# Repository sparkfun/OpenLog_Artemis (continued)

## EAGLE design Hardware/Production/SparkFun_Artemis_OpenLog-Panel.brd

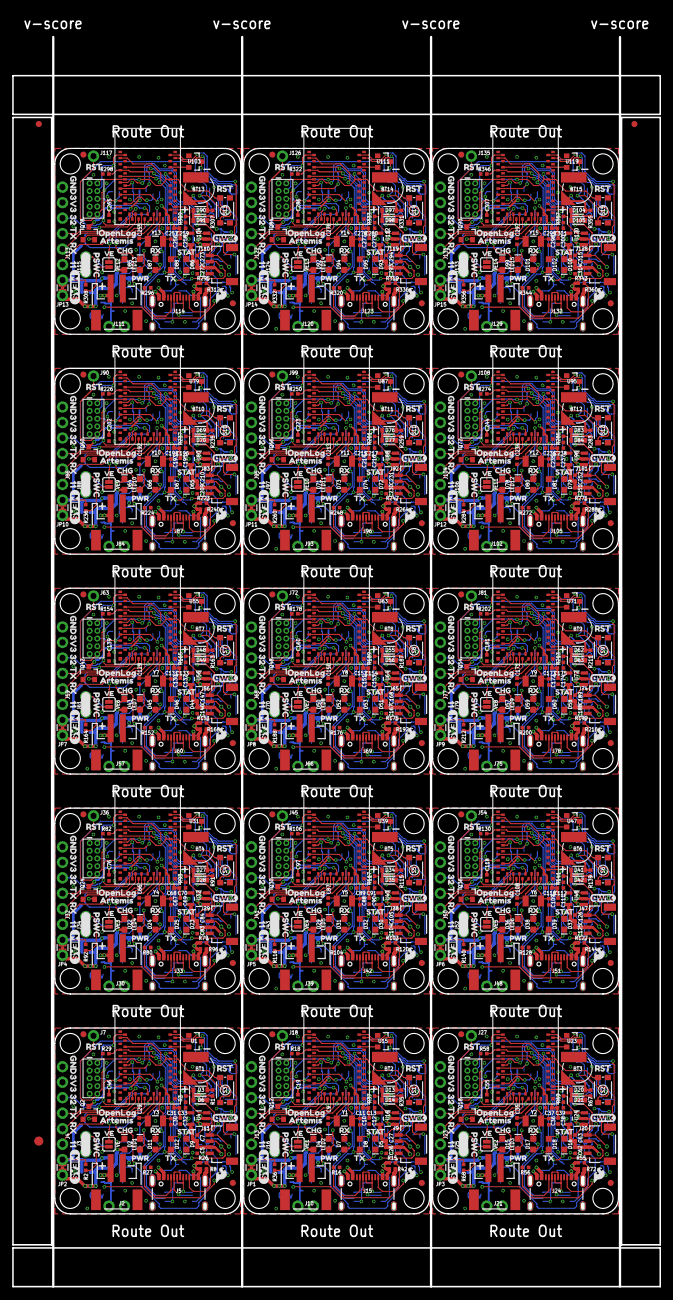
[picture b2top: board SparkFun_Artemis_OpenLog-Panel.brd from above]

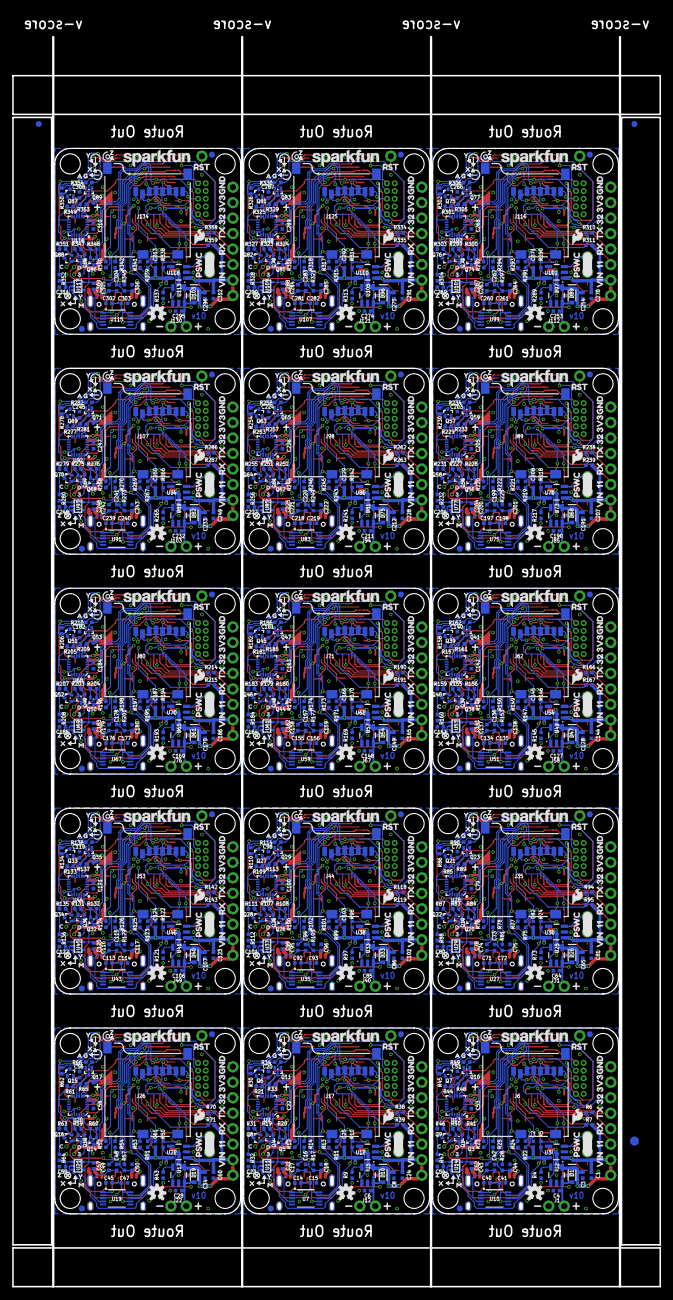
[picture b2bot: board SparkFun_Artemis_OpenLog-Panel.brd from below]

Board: 4 copper layers, 106.2 x 205.0 mm, 2076 parts (1113 on the bottom side), 915 nets.

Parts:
BT1, BT2, BT3, BT4, BT5, BT6, BT7, BT8, BT9, BT10, BT11, BT12, BT13, BT14, BT15: ML414H; ML414H_IV01E
C1, C13, C22, C23, C24, C33, C39, C53, C54, C58, C59, C60, C70, C79, C80, C81, C91, C100, C101, C102, C112, C121, C122, C123, C133, C142, C143, C144, C154, C163, C164, C165, C175, C184, C185, C186, C196, C205, C206, C207, C217, C226, C227, C228, C238, C247, C248, C249, C259, C268, C269, C270, C280, C289, C290, C291, C301, C310, C311, C312: 1.0uF; 0402-TIGHT
C2, C7, C25, C27, C61, C63, C82, C84, C103, C105, C124, C126, C145, C147, C166, C168, C187, C189, C208, C210, C229, C231, C250, C252, C271, C273, C292, C294, C313, C315: 2.2uF; 0402-TIGHT
C3, C4, C6, C8, C28, C34, C64, C65, C85, C86, C106, C107, C127, C128, C148, C149, C169, C170, C190, C191, C211, C212, C232, C233, C253, C254, C274, C275, C295, C296: 4.7uF; 0402-TIGHT
C5, C11, C15, C16, C17, C19, C20, C21, C26, C31, C37, C41, C42, C43, C46, C47, C48, C49, C51, C52, C55, C56, C57, C62, C68, C72, C73, C74, C76, C77, C78, C83, C89, C93, C94, C95, C97, C98, C99, C104, C110, C114, C115, C116, C118, C119, C120, C125, C131, C135, C136, C137, C139, C140, C141, C146, C152, C156, C157, C158, C160, C161, C162, C167, C173, C177, C178, C179, C181, C182, C183, C188, C194, C198, C199, C200, C202, C203, C204, C209, C215, C219, C220, C221, C223, C224, C225, C230, C236, C240, C241, C242, C244, C245, C246, C251, C257, C261, C262, C263, C265, C266, C267, C272, C278, C282, C283, C284, C286, C287, C288, C293, C299, C303, C304, C305, C307, C308, C309, C314: 0.1uF; 0402-TIGHT
C9, C10, C29, C30, C35, C36, C66, C67, C87, C88, C108, C109, C129, C130, C150, C151, C171, C172, C192, C193, C213, C214, C234, C235, C255, C256, C276, C277, C297, C298: 15pF; 0402-TIGHT
C12, C32, C38, C69, C90, C111, C132, C153, C174, C195, C216, C237, C258, C279, C300: 10uF; 0402-TIGHT
C14, C40, C45, C71, C92, C113, C134, C155, C176, C197, C218, C239, C260, C281, C302: 10nF; 0402-TIGHT
C18, C44, C50, C75, C96, C117, C138, C159, C180, C201, C222, C243, C264, C285, C306: 1.0nF; 0402-TIGHT
D1, D3, D10, D13, D19, D20, D26, D27, D33, D34, D40, D41, D47, D48, D54, D55, D61, D62, D68, D69, D75, D76, D82, D83, D89, D90, D96, D97, D103, D104: 3A/10V/280mV; SOD-323
D2, D4, D7, D11, D15, D17, D22, D24, D29, D31, D36, D38, D43, D45, D50, D52, D57, D59, D64, D66, D71, D73, D78, D80, D85, D87, D92, D94, D99, D101: Yellow; LED-0603
D5, D9, D16, D23, D30, D37, D44, D51, D58, D65, D72, D79, D86, D93, D100: BLUE; LED-0603
D6, D14, D21, D28, D35, D42, D49, D56, D63, D70, D77, D84, D91, D98, D105: 1A/23V/620mV; SOD-323
D8, D12, D18, D25, D32, D39, D46, D53, D60, D67, D74, D81, D88, D95, D102: GREEN; LED-0603
E$1, E$2, E$3, E$4: FIDUCIAL-1X2
E$5, E$6: FIDUCIAL-1.5X3
FD1, FD2, FD3, FD4, FD5, FD6, FD7, FD8, FD9, FD10, FD11, FD12, FD13, FD14, FD15, FD16, FD17, FD18, FD19, FD20, FD21, FD22, FD23, FD24, FD25, FD26, FD27, FD28, FD29, FD30, FD31, FD32, FD33, FD34, FD35, FD36, FD37, FD38, FD39, FD40, FD41, FD42, FD43, FD44, FD45, FD46, FD47, FD48, FD49, FD50, FD51, FD52, FD53, FD54, FD55, FD56, FD57, FD58, FD59, FD60: FIDUCIAL1X2; FIDUCIAL-1X2
GND, GND1, GND2, GND3, GND4, GND5, GND6, GND7, GND8, GND9, GND10, GND11, GND12, GND13, GND14: TEST-POINTTP_15TH_THRU; TP_15TH
H1, H2, H3, H4, H5, H6, H7, H8, H9, H10, H11, H12, H13, H14, H15, H16, H17, H18, H19, H20, H21, H22, H23, H24, H25, H26, H27, H28, H29, H30, H31, H32, H33, H34, H35, H36, H37, H38, H39, H40, H41, H42, H43, H44, H45, H46, H47, H48, H49, H50, H51, H52, H53, H54, H55, H56, H57, H58, H59, H60: STAND-OFF
J1, J3, J12, J16, J22, J25, J31, J34, J40, J43, J49, J52, J58, J61, J67, J70, J76, J79, J85, J88, J94, J97, J103, J106, J112, J115, J121, J124, J130, J133: 1X02_NO_SILK
J2, J10, J21, J30, J39, J48, J57, J66, J75, J84, J93, J102, J111, J120, J129: JST-2-SMD
J4, J13, J23, J32, J41, J50, J59, J68, J77, J86, J95, J104, J113, J122, J131: 1X06_NO_SILK
J5, J15, J24, J33, J42, J51, J60, J69, J78, J87, J96, J105, J114, J123, J132: USB-C-16P_4LAYER-PADS
J6, J17, J26, J35, J44, J53, J62, J71, J80, J89, J98, J107, J116, J125, J134: MICRO-SD; MICRO-SD-SOCKET
J7, J18, J27, J36, J45, J54, J63, J72, J81, J90, J99, J108, J117, J126, J135: 1X01_NO_SILK
J8, J14, J19, J28, J37, J46, J55, J64, J73, J82, J91, J100, J109, J118, J127: CORTEX_JTAG; 2X5-PTH-1.27MM
J9, J11, J20, J29, J38, J47, J56, J65, J74, J83, J92, J101, J110, J119, J128: JST04_1MM_RA
JP1, JP2, JP3, JP4, JP5, JP6, JP7, JP8, JP9, JP10, JP11, JP12, JP13, JP14, JP15: MEAS; COMBO-JUMPER_2_NC_TRACE
LED1, LED2, LED3, LED4, LED5, LED6, LED7, LED8, LED9, LED10, LED11, LED12, LED13, LED14, LED15: RED; LED-0603
LOGO1, LOGO7, LOGO11, LOGO15, LOGO19, LOGO23, LOGO27, LOGO31, LOGO35, LOGO39, LOGO43, LOGO47, LOGO51, LOGO55, LOGO59: SFE_LOGO_NAME.1_INCH; SFE_LOGO_NAME_.1
LOGO2, LOGO3, LOGO9, LOGO13, LOGO17, LOGO21, LOGO25, LOGO29, LOGO33, LOGO37, LOGO41, LOGO45, LOGO49, LOGO53, LOGO57: OSHW-LOGOS; OSHW-LOGO-S
LOGO4, LOGO5, LOGO6, LOGO8, LOGO10, LOGO12, LOGO14, LOGO16, LOGO18, LOGO20, LOGO22, LOGO24, LOGO26, LOGO28, LOGO30, LOGO32, LOGO34, LOGO36, LOGO38, LOGO40, LOGO42, LOGO44, LOGO46, LOGO48, LOGO50, LOGO52, LOGO54, LOGO56, LOGO58, LOGO60: SFE_LOGO_FLAME.1_INCH; SFE_LOGO_FLAME_.1
Q1, Q3, Q4, Q5, Q6, Q7, Q8, Q9, Q10, Q11, Q13, Q14, Q15, Q16, Q17, Q19, Q20, Q21, Q22, Q23, Q25, Q26, Q27, Q28, Q29, Q31, Q32, Q33, Q34, Q35, Q37, Q38, Q39, Q40, Q41, Q43, Q44, Q45, Q46, Q47, Q49, Q50, Q51, Q52, Q53, Q55, Q56, Q57, Q58, Q59, Q61, Q62, Q63, Q64, Q65, Q67, Q68, Q69, Q70, Q71, Q73, Q74, Q75, Q76, Q77, Q79, Q80, Q81, Q82, Q83, Q85, Q86, Q87, Q88, Q89: 20V/0.2A/8MHz/1.2Ω/1Vth; SOT-416FL
Q2, Q12, Q18, Q24, Q30, Q36, Q42, Q48, Q54, Q60, Q66, Q72, Q78, Q84, Q90: 20V/4.2A/52mΩ/1.4W; SOT23-3
QWIIC_3.3V, QWIIC_3.3V1, QWIIC_3.3V2, QWIIC_3.3V3, QWIIC_3.3V4, QWIIC_3.3V5, QWIIC_3.3V6, QWIIC_3.3V7, QWIIC_3.3V8, QWIIC_3.3V9, QWIIC_3.3V10, QWIIC_3.3V11, QWIIC_3.3V12, QWIIC_3.3V13, QWIIC_3.3V14: TEST-POINTTP_15TH_THRU; TP_15TH
R1, R5, R10, R11, R12, R13, R14, R22, R23, R24, R25, R35, R50, R51, R52, R53, R54, R67, R74, R75, R76, R77, R78, R91, R98, R99, R100, R101, R102, R115, R122, R123, R124, R125, R126, R139, R146, R147, R148, R149, R150, R163, R170, R171, R172, R173, R174, R187, R194, R195, R196, R197, R198, R211, R218, R219, R220, R221, R222, R235, R242, R243, R244, R245, R246, R259, R266, R267, R268, R269, R270, R283, R290, R291, R292, R293, R294, R307, R314, R315, R316, R317, R318, R331, R338, R339, R340, R341, R342, R355: 1k; 0402-TIGHT
R2, R36, R68, R92, R116, R140, R164, R188, R212, R236, R260, R284, R308, R332, R356: 330K; 0402-TIGHT
R3, R37, R69, R93, R117, R141, R165, R189, R213, R237, R261, R285, R309, R333, R357: 220k; 0402-TIGHT
R4, R9, R19, R20, R21, R30, R31, R32, R33, R40, R41, R43, R44, R45, R46, R47, R48, R59, R60, R61, R62, R63, R64, R65, R73, R83, R84, R85, R86, R87, R88, R89, R97, R107, R108, R109, R110, R111, R112, R113, R121, R131, R132, R133, R134, R135, R136, R137, R145, R155, R156, R157, R158, R159, R160, R161, R169, R179, R180, R181, R182, R183, R184, R185, R193, R203, R204, R205, R206, R207, R208, R209, R217, R227, R228, R229, R230, R231, R232, R233, R241, R251, R252, R253, R254, R255, R256, R257, R265, R275, R276, R277, R278, R279, R280, R281, R289, R299, R300, R301, R302, R303, R304, R305, R313, R323, R324, R325, R326, R327, R328, R329, R337, R347, R348, R349, R350, R351, R352, R353: 2.2k; 0402-TIGHT
R6, R38, R70, R94, R118, R142, R166, R190, R214, R238, R262, R286, R310, R334, R358: 1M; 0402-TIGHT
R7, R39, R71, R95, R119, R143, R167, R191, R215, R239, R263, R287, R311, R335, R359: 2M; 0402-TIGHT
R8, R42, R72, R96, R120, R144, R168, R192, R216, R240, R264, R288, R312, R336, R360: 0; 0402-TIGHT
R15, R16, R26, R27, R55, R56, R79, R80, R103, R104, R127, R128, R151, R152, R175, R176, R199, R200, R223, R224, R247, R248, R271, R272, R295, R296, R319, R320, R343, R344: 5.1k; 0402-TIGHT
R17, R28, R57, R81, R105, R129, R153, R177, R201, R225, R249, R273, R297, R321, R345: 100k; 0402-TIGHT
R18, R29, R58, R82, R106, R130, R154, R178, R202, R226, R250, R274, R298, R322, R346: 220KOHM-0402T-1/16W-1%; 0402-TIGHT
R34, R49, R66, R90, R114, R138, R162, R186, R210, R234, R258, R282, R306, R330, R354: DNP; 0402-TIGHT
S1, S2, S3, S4, S5, S6, S7, S8, S9, S10, S11, S12, S13, S14, S15: RESET; TACTILE_SWITCH_SMD_4.6X2.8MM
SCL, SCL1, SCL2, SCL3, SCL4, SCL5, SCL6, SCL7, SCL8, SCL9, SCL10, SCL11, SCL12, SCL13, SCL14: TEST-POINTTP_15TH_THRU; TP_15TH
SDA, SDA1, SDA2, SDA3, SDA4, SDA5, SDA6, SDA7, SDA8, SDA9, SDA10, SDA11, SDA12, SDA13, SDA14: TEST-POINTTP_15TH_THRU; TP_15TH
TP1, TP2, TP3, TP4, TP5, TP6, TP7, TP8, TP9, TP10, TP11, TP12, TP13, TP14, TP15: TEST-POINT3; PAD.03X.03
U1, U15, U23, U31, U39, U47, U55, U63, U71, U79, U87, U95, U103, U111, U119: 3.0V Supervisor; SOT23-3
U2, U5, U17, U25, U33, U41, U49, U57, U65, U73, U81, U89, U97, U105, U113: MCP73831; SOT23-5
U3, U4, U12, U16, U22, U24, U30, U32, U38, U40, U46, U48, U54, U56, U62, U64, U70, U72, U78, U80, U86, U88, U94, U96, U102, U104, U110, U112, U118, U120: 3.3V; SOT23-5
U6, U8, U18, U26, U34, U42, U50, U58, U66, U74, U82, U90, U98, U106, U114: ARTEMIS_MODULE; ARTEMIS_FP
U7, U10, U19, U27, U35, U43, U51, U59, U67, U75, U83, U91, U99, U107, U115: CH340E; MSOP10
U9, U13, U20, U28, U36, U44, U52, U60, U68, U76, U84, U92, U100, U108, U116: 9DoF IMU; QFN24-3X3-ICM-20948
U11, U14, U21, U29, U37, U45, U53, U61, U69, U77, U85, U93, U101, U109, U117: 1.8V/100mA; SC70
U$1, U$26, U$91, U$131, U$171, U$211, U$251, U$291, U$331, U$371, U$411, U$451, U$491, U$531, U$571: QWIIC#LOGO#JPG
U$2, U$29, U$92, U$132, U$172, U$212, U$252, U$292, U$332, U$372, U$412, U$452, U$492, U$532, U$572: CHG2
U$3, U$30, U$93, U$133, U$173, U$213, U$253, U$293, U$333, U$373, U$413, U$453, U$493, U$533, U$573: PWR0
U$4, U$31, U$94, U$134, U$174, U$214, U$254, U$294, U$334, U$374, U$414, U$454, U$494, U$534, U$574: RX4
U$5, U$52, U$95, U$135, U$175, U$215, U$255, U$295, U$335, U$375, U$415, U$455, U$495, U$535, U$575: STAT5
U$6, U$75, U$115, U$155, U$195, U$235, U$275, U$315, U$355, U$395, U$435, U$475, U$515, U$555, U$595: VE0
U$7, U$53, U$96, U$136, U$176, U$216, U$256, U$296, U$336, U$376, U$416, U$456, U$496, U$536, U$576: TX3
U$8, U$12, U$76, U$77, U$116, U$117, U$156, U$157, U$196, U$197, U$236, U$237, U$276, U$277, U$316, U$317, U$356, U$357, U$396, U$397, U$436, U$437, U$476, U$477, U$516, U$517, U$556, U$557, U$596, U$597: RST0
U$9, U$57, U$97, U$137, U$177, U$217, U$257, U$297, U$337, U$377, U$417, U$457, U$497, U$537, U$577: ARTEMIS13
U$10, U$11, U$73, U$74, U$113, U$114, U$153, U$154, U$193, U$194, U$233, U$234, U$273, U$274, U$313, U$314, U$353, U$354, U$393, U$394, U$433, U$434, U$473, U$474, U$513, U$514, U$553, U$554, U$593, U$594: PSWC0
U$13, U$78, U$118, U$158, U$198, U$238, U$278, U$318, U$358, U$398, U$438, U$478, U$518, U$558, U$598: C0
U$14, U$79, U$119, U$159, U$199, U$239, U$279, U$319, U$359, U$399, U$439, U$479, U$519, U$559, U$599: D0
U$15, U$80, U$120, U$160, U$200, U$240, U$280, U$320, U$360, U$400, U$440, U$480, U$520, U$560, U$600: 30
U$16, U$27, U$81, U$121, U$161, U$201, U$241, U$281, U$321, U$361, U$401, U$441, U$481, U$521, U$561: MEAS3
U$17, U$23, U$43, U$49, U$82, U$88, U$122, U$128, U$162, U$168, U$202, U$208, U$242, U$248, U$282, U$288, U$322, U$328, U$362, U$368, U$402, U$408, U$442, U$448, U$482, U$488, U$522, U$528, U$562, U$568: X0
U$18, U$24, U$44, U$50, U$83, U$89, U$123, U$129, U$163, U$169, U$203, U$209, U$243, U$249, U$283, U$289, U$323, U$329, U$363, U$369, U$403, U$409, U$443, U$449, U$483, U$489, U$523, U$529, U$563, U$569: Y1
U$19, U$25, U$45, U$51, U$84, U$90, U$124, U$130, U$164, U$170, U$204, U$210, U$244, U$250, U$284, U$290, U$324, U$330, U$364, U$370, U$404, U$410, U$444, U$450, U$484, U$490, U$524, U$530, U$564, U$570: Z2
U$20, U$46, U$85, U$125, U$165, U$205, U$245, U$285, U$325, U$365, U$405, U$445, U$485, U$525, U$565: G5
U$21, U$47, U$86, U$126, U$166, U$206, U$246, U$286, U$326, U$366, U$406, U$446, U$486, U$526, U$566: A4
U$22, U$48, U$87, U$127, U$167, U$207, U$247, U$287, U$327, U$367, U$407, U$447, U$487, U$527, U$567: M3
U$28, U$58, U$98, U$138, U$178, U$218, U$258, U$298, U$338, U$378, U$418, U$458, U$498, U$538, U$578: OPENLOG12
U$32, U$59, U$99, U$139, U$179, U$219, U$259, U$299, U$339, U$379, U$419, U$459, U$499, U$539, U$579: RST9
U$33, U$60, U$100, U$140, U$180, U$220, U$260, U$300, U$340, U$380, U$420, U$460, U$500, U$540, U$580: VIN8
U$34, U$35, U$61, U$62, U$101, U$102, U$141, U$142, U$181, U$182, U$221, U$222, U$261, U$262, U$301, U$302, U$341, U$342, U$381, U$382, U$421, U$422, U$461, U$462, U$501, U$502, U$541, U$542, U$581, U$582: 3V34
U$36, U$37, U$63, U$64, U$103, U$104, U$143, U$144, U$183, U$184, U$223, U$224, U$263, U$264, U$303, U$304, U$343, U$344, U$383, U$384, U$423, U$424, U$463, U$464, U$503, U$504, U$543, U$544, U$583, U$584: 113
U$38, U$39, U$65, U$66, U$105, U$106, U$145, U$146, U$185, U$186, U$225, U$226, U$265, U$266, U$305, U$306, U$345, U$346, U$385, U$386, U$425, U$426, U$465, U$466, U$505, U$506, U$545, U$546, U$585, U$586: 322
U$40, U$41, U$67, U$68, U$107, U$108, U$147, U$148, U$187, U$188, U$227, U$228, U$267, U$268, U$307, U$308, U$347, U$348, U$387, U$388, U$427, U$428, U$467, U$468, U$507, U$508, U$547, U$548, U$587, U$588: GND5
U$42, U$54, U$69, U$70, U$109, U$110, U$149, U$150, U$189, U$190, U$229, U$230, U$269, U$270, U$309, U$310, U$349, U$350, U$389, U$390, U$429, U$430, U$469, U$470, U$509, U$510, U$549, U$550, U$589, U$590: RX1
U$55, U$56, U$71, U$72, U$111, U$112, U$151, U$152, U$191, U$192, U$231, U$232, U$271, U$272, U$311, U$312, U$351, U$352, U$391, U$392, U$431, U$432, U$471, U$472, U$511, U$512, U$551, U$552, U$591, U$592: TX0
VE, VE1, VE2, VE3, VE4, VE5, VE6, VE7, VE8, VE9, VE10, VE11, VE12, VE13, VE14: SMT-JUMPER_2_NO_SILK
Y1, Y2, Y3, Y4, Y5, Y6, Y7, Y8, Y9, Y10, Y11, Y12, Y13, Y14, Y15: 32.768kHz; CRYSTAL-SMD-3.2X1.5MM

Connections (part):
3.3V: C2.1, C40.1, C41.1, C54.1, D6.A, J4.5, J14.1, Q2.2, R24.2, R25.2, R45.2, R47.2, R49.2, U1.3, U3.5, U10.7, U10.10, U14.1
3.3V1: C14.1, C15.1, C23.1, C25.1, D14.A, J8.1, J13.5, Q12.2, R13.2, R14.2, R30.2, R32.2, R34.2, U7.7, U7.10, U11.1, U12.5, U15.3
3.3V2: C45.1, C47.1, C59.1, C61.1, D21.A, J19.1, J23.5, Q18.2, R53.2, R54.2, R62.2, R64.2, R66.2, U19.7, U19.10, U21.1, U22.5, U23.3
3.3V3: C71.1, C72.1, C80.1, C82.1, D28.A, J28.1, J32.5, Q24.2, R77.2, R78.2, R86.2, R88.2, R90.2, U27.7, U27.10, U29.1, U30.5, U31.3
3.3V4: C92.1, C93.1, C101.1, C103.1, D35.A, J37.1, J41.5, Q30.2, R101.2, R102.2, R110.2, R112.2, R114.2, U35.7, U35.10, U37.1, U38.5, U39.3
3.3V5: C113.1, C114.1, C122.1, C124.1, D42.A, J46.1, J50.5, Q36.2, R125.2, R126.2, R134.2, R136.2, R138.2, U43.7, U43.10, U45.1, U46.5, U47.3
3.3V6: C134.1, C135.1, C143.1, C145.1, D49.A, J55.1, J59.5, Q42.2, R149.2, R150.2, R158.2, R160.2, R162.2, U51.7, U51.10, U53.1, U54.5, U55.3
3.3V7: C155.1, C156.1, C164.1, C166.1, D56.A, J64.1, J68.5, Q48.2, R173.2, R174.2, R182.2, R184.2, R186.2, U59.7, U59.10, U61.1, U62.5, U63.3
3.3V8: C176.1, C177.1, C185.1, C187.1, D63.A, J73.1, J77.5, Q54.2, R197.2, R198.2, R206.2, R208.2, R210.2, U67.7, U67.10, U69.1, U70.5, U71.3
3.3V9: C197.1, C198.1, C206.1, C208.1, D70.A, J82.1, J86.5, Q60.2, R221.2, R222.2, R230.2, R232.2, R234.2, U75.7, U75.10, U77.1, U78.5, U79.3
3.3V10: C218.1, C219.1, C227.1, C229.1, D77.A, J91.1, J95.5, Q66.2, R245.2, R246.2, R254.2, R256.2, R258.2, U83.7, U83.10, U85.1, U86.5, U87.3
3.3V11: C239.1, C240.1, C248.1, C250.1, D84.A, J100.1, J104.5, Q72.2, R269.2, R270.2, R278.2, R280.2, R282.2, U91.7, U91.10, U93.1, U94.5, U95.3
3.3V12: C260.1, C261.1, C269.1, C271.1, D91.A, J109.1, J113.5, Q78.2, R293.2, R294.2, R302.2, R304.2, R306.2, U99.7, U99.10, U101.1, U102.5, U103.3
3.3V13: C281.1, C282.1, C290.1, C292.1, D98.A, J118.1, J122.5, Q84.2, R317.2, R318.2, R326.2, R328.2, R330.2, U107.7, U107.10, U109.1, U110.5, U111.3
3.3V14: C302.1, C303.1, C311.1, C313.1, D105.A, J127.1, J131.5, Q90.2, R341.2, R342.2, R350.2, R352.2, R354.2, U115.7, U115.10, U117.1, U118.5, U119.3
5V: C3.1, D1.C, D2.A, J5.VBUS1, J5.VBUS2, JP2.1, JP2.3, U2.4
5V1: C8.1, D4.A, D10.C, J15.VBUS1, J15.VBUS2, JP1.1, JP1.3, U5.4
5V2: C34.1, D15.A, D19.C, J24.VBUS1, J24.VBUS2, JP3.1, JP3.3, U17.4
5V3: C65.1, D22.A, D26.C, J33.VBUS1, J33.VBUS2, JP4.1, JP4.3, U25.4
5V4: C86.1, D29.A, D33.C, J42.VBUS1, J42.VBUS2, JP5.1, JP5.3, U33.4
5V5: C107.1, D36.A, D40.C, J51.VBUS1, J51.VBUS2, JP6.1, JP6.3, U41.4
5V6: C128.1, D43.A, D47.C, J60.VBUS1, J60.VBUS2, JP7.1, JP7.3, U49.4
5V7: C149.1, D50.A, D54.C, J69.VBUS1, J69.VBUS2, JP8.1, JP8.3, U57.4
5V8: C170.1, D57.A, D61.C, J78.VBUS1, J78.VBUS2, JP9.1, JP9.3, U65.4
5V9: C191.1, D64.A, D68.C, J87.VBUS1, J87.VBUS2, JP10.1, JP10.3, U73.4
5V10: C212.1, D71.A, D75.C, J96.VBUS1, J96.VBUS2, JP11.1, JP11.3, U81.4
5V11: C233.1, D78.A, D82.C, J105.VBUS1, J105.VBUS2, JP12.1, JP12.3, U89.4
5V12: C254.1, D85.A, D89.C, J114.VBUS1, J114.VBUS2, JP13.1, JP13.3, U97.4
5V13: C275.1, D92.A, D96.C, J123.VBUS1, J123.VBUS2, JP14.1, JP14.3, U105.4
5V14: C296.1, D99.A, D103.C, J132.VBUS1, J132.VBUS2, JP15.1, JP15.3, U113.4
!POWER_LOSS!: U1.2, U8.D3
!POWER_LOSS!1: U6.D3, U15.2
!POWER_LOSS!2: U18.D3, U23.2
!POWER_LOSS!3: U26.D3, U31.2
!POWER_LOSS!4: U34.D3, U39.2
!POWER_LOSS!5: U42.D3, U47.2
!POWER_LOSS!6: U50.D3, U55.2
!POWER_LOSS!7: U58.D3, U63.2
!POWER_LOSS!8: U66.D3, U71.2
!POWER_LOSS!9: U74.D3, U79.2
!POWER_LOSS!10: U82.D3, U87.2
!POWER_LOSS!11: U90.D3, U95.2
!POWER_LOSS!12: U98.D3, U103.2
!POWER_LOSS!13: U106.D3, U111.2
!POWER_LOSS!14: U114.D3, U119.2
ARTEMIS_!RESET: C42.2, C44.1, J7.1, J14.10, R28.1, S3.3, S3.4, U8.~RST
ARTEMIS_!RESET1: C16.2, C18.1, J8.10, J18.1, R17.1, S1.3, S1.4, U6.~RST
ARTEMIS_!RESET2: C48.2, C50.1, J19.10, J27.1, R57.1, S2.3, S2.4, U18.~RST
ARTEMIS_!RESET3: C73.2, C75.1, J28.10, J36.1, R81.1, S4.3, S4.4, U26.~RST
ARTEMIS_!RESET4: C94.2, C96.1, J37.10, J45.1, R105.1, S5.3, S5.4, U34.~RST
ARTEMIS_!RESET5: C115.2, C117.1, J46.10, J54.1, R129.1, S6.3, S6.4, U42.~RST
ARTEMIS_!RESET6: C136.2, C138.1, J55.10, J63.1, R153.1, S7.3, S7.4, U50.~RST
ARTEMIS_!RESET7: C157.2, C159.1, J64.10, J72.1, R177.1, S8.3, S8.4, U58.~RST
ARTEMIS_!RESET8: C178.2, C180.1, J73.10, J81.1, R201.1, S9.3, S9.4, U66.~RST
ARTEMIS_!RESET9: C199.2, C201.1, J82.10, J90.1, R225.1, S10.3, S10.4, U74.~RST
ARTEMIS_!RESET10: C220.2, C222.1, J91.10, J99.1, R249.1, S11.3, S11.4, U82.~RST
ARTEMIS_!RESET11: C241.2, C243.1, J100.10, J108.1, R273.1, S12.3, S12.4, U90.~RST
ARTEMIS_!RESET12: C262.2, C264.1, J109.10, J117.1, R297.1, S13.3, S13.4, U98.~RST
ARTEMIS_!RESET13: C283.2, C285.1, J118.10, J126.1, R321.1, S14.3, S14.4, U106.~RST
ARTEMIS_!RESET14: C304.2, C306.1, J127.10, J135.1, R345.1, S15.3, S15.4, U114.~RST
ARTEMIS_!RTS!: C42.1, C43.1, U10.4
ARTEMIS_!RTS!1: C16.1, C17.1, U7.4
ARTEMIS_!RTS!2: C48.1, C49.1, U19.4
ARTEMIS_!RTS!3: C73.1, C74.1, U27.4
ARTEMIS_!RTS!4: C94.1, C95.1, U35.4
ARTEMIS_!RTS!5: C115.1, C116.1, U43.4
ARTEMIS_!RTS!6: C136.1, C137.1, U51.4
ARTEMIS_!RTS!7: C157.1, C158.1, U59.4
ARTEMIS_!RTS!8: C178.1, C179.1, U67.4
ARTEMIS_!RTS!9: C199.1, C200.1, U75.4
ARTEMIS_!RTS!10: C220.1, C221.1, U83.4
ARTEMIS_!RTS!11: C241.1, C242.1, U91.4
ARTEMIS_!RTS!12: C262.1, C263.1, U99.4
ARTEMIS_!RTS!13: C283.1, C284.1, U107.4
ARTEMIS_!RTS!14: C304.1, C305.1, U115.4
ARTEMIS_BOOT: C43.2, R29.2, U8.BOOT
ARTEMIS_BOOT1: C17.2, R18.2, U6.BOOT
ARTEMIS_BOOT2: C49.2, R58.2, U18.BOOT
ARTEMIS_BOOT3: C74.2, R82.2, U26.BOOT
ARTEMIS_BOOT4: C95.2, R106.2, U34.BOOT
ARTEMIS_BOOT5: C116.2, R130.2, U42.BOOT
ARTEMIS_BOOT6: C137.2, R154.2, U50.BOOT
ARTEMIS_BOOT7: C158.2, R178.2, U58.BOOT
ARTEMIS_BOOT8: C179.2, R202.2, U66.BOOT
ARTEMIS_BOOT9: C200.2, R226.2, U74.BOOT
ARTEMIS_BOOT10: C221.2, R250.2, U82.BOOT
ARTEMIS_BOOT11: C242.2, R274.2, U90.BOOT
ARTEMIS_BOOT12: C263.2, R298.2, U98.BOOT
ARTEMIS_BOOT13: C284.2, R322.2, U106.BOOT
ARTEMIS_BOOT14: C305.2, R346.2, U114.BOOT
ARTEMIS_RX0: D11.C, U8.RXI-0, U10.8
ARTEMIS_RX1: D7.C, U6.RXI-0, U7.8
ARTEMIS_RX2: D17.C, U18.RXI-0, U19.8
ARTEMIS_RX3: D24.C, U26.RXI-0, U27.8
ARTEMIS_RX4: D31.C, U34.RXI-0, U35.8
ARTEMIS_RX5: D38.C, U42.RXI-0, U43.8
ARTEMIS_RX6: D45.C, U50.RXI-0, U51.8
ARTEMIS_RX7: D52.C, U58.RXI-0, U59.8
ARTEMIS_RX8: D59.C, U66.RXI-0, U67.8
ARTEMIS_RX9: D66.C, U74.RXI-0, U75.8
ARTEMIS_RX10: D73.C, U82.RXI-0, U83.8
ARTEMIS_RX11: D80.C, U90.RXI-0, U91.8
ARTEMIS_RX12: D87.C, U98.RXI-0, U99.8
ARTEMIS_RX13: D94.C, U106.RXI-0, U107.8
ARTEMIS_RX14: D101.C, U114.RXI-0, U115.8
ARTEMIS_SWDCK: J14.4, U8.SWDCK
ARTEMIS_SWDCK1: J8.4, U6.SWDCK
ARTEMIS_SWDCK2: J19.4, U18.SWDCK
ARTEMIS_SWDCK3: J28.4, U26.SWDCK
ARTEMIS_SWDCK4: J37.4, U34.SWDCK
ARTEMIS_SWDCK5: J46.4, U42.SWDCK
ARTEMIS_SWDCK6: J55.4, U50.SWDCK
ARTEMIS_SWDCK7: J64.4, U58.SWDCK
ARTEMIS_SWDCK8: J73.4, U66.SWDCK
ARTEMIS_SWDCK9: J82.4, U74.SWDCK
ARTEMIS_SWDCK10: J91.4, U82.SWDCK
ARTEMIS_SWDCK11: J100.4, U90.SWDCK
ARTEMIS_SWDCK12: J109.4, U98.SWDCK
ARTEMIS_SWDCK13: J118.4, U106.SWDCK
ARTEMIS_SWDCK14: J127.4, U114.SWDCK
ARTEMIS_SWDIO: J14.2, U8.SWDIO
ARTEMIS_SWDIO1: J8.2, U6.SWDIO
ARTEMIS_SWDIO2: J19.2, U18.SWDIO
ARTEMIS_SWDIO3: J28.2, U26.SWDIO
ARTEMIS_SWDIO4: J37.2, U34.SWDIO
ARTEMIS_SWDIO5: J46.2, U42.SWDIO
ARTEMIS_SWDIO6: J55.2, U50.SWDIO
ARTEMIS_SWDIO7: J64.2, U58.SWDIO
ARTEMIS_SWDIO8: J73.2, U66.SWDIO
ARTEMIS_SWDIO9: J82.2, U74.SWDIO
ARTEMIS_SWDIO10: J91.2, U82.SWDIO
ARTEMIS_SWDIO11: J100.2, U90.SWDIO
ARTEMIS_SWDIO12: J109.2, U98.SWDIO
ARTEMIS_SWDIO13: J118.2, U106.SWDIO
ARTEMIS_SWDIO14: J127.2, U114.SWDIO
ARTEMIS_TX0: D12.C, U8.TXO-0, U10.9
ARTEMIS_TX1: D8.C, U6.TXO-0, U7.9
ARTEMIS_TX2: D18.C, U18.TXO-0, U19.9
ARTEMIS_TX3: D25.C, U26.TXO-0, U27.9
ARTEMIS_TX4: D32.C, U34.TXO-0, U35.9
ARTEMIS_TX5: D39.C, U42.TXO-0, U43.9
ARTEMIS_TX6: D46.C, U50.TXO-0, U51.9
ARTEMIS_TX7: D53.C, U58.TXO-0, U59.9
ARTEMIS_TX8: D60.C, U66.TXO-0, U67.9
ARTEMIS_TX9: D67.C, U74.TXO-0, U75.9
ARTEMIS_TX10: D74.C, U82.TXO-0, U83.9
ARTEMIS_TX11: D81.C, U90.TXO-0, U91.9
ARTEMIS_TX12: D88.C, U98.TXO-0, U99.9
ARTEMIS_TX13: D95.C, U106.TXO-0, U107.9
ARTEMIS_TX14: D102.C, U114.TXO-0, U115.9
ARTEMIS_~AD1: J13.1, U6.~AD11
ARTEMIS_~AD2: J13.4, U6.~AD32
ARTEMIS_~AD3: J23.1, U18.~AD11
ARTEMIS_~AD4: J23.4, U18.~AD32
ARTEMIS_~AD5: J32.1, U26.~AD11
ARTEMIS_~AD6: J32.4, U26.~AD32
ARTEMIS_~AD7: J41.1, U34.~AD11
ARTEMIS_~AD8: J41.4, U34.~AD32
ARTEMIS_~AD9: J50.1, U42.~AD11
ARTEMIS_~AD10: J50.4, U42.~AD32
ARTEMIS_~AD11: J4.1, U8.~AD11
ARTEMIS_~AD12: J59.1, U50.~AD11
ARTEMIS_~AD12/TX1: J4.3, U8.~AD12
ARTEMIS_~AD12/TX2: J13.3, U6.~AD12
ARTEMIS_~AD12/TX3: J23.3, U18.~AD12
ARTEMIS_~AD12/TX4: J32.3, U26.~AD12
ARTEMIS_~AD12/TX5: J41.3, U34.~AD12
ARTEMIS_~AD12/TX6: J50.3, U42.~AD12
ARTEMIS_~AD12/TX7: J59.3, U50.~AD12
ARTEMIS_~AD12/TX8: J68.3, U58.~AD12
ARTEMIS_~AD12/TX9: J77.3, U66.~AD12
ARTEMIS_~AD12/TX10: J86.3, U74.~AD12
ARTEMIS_~AD12/TX11: J95.3, U82.~AD12
ARTEMIS_~AD12/TX12: J104.3, U90.~AD12
ARTEMIS_~AD12/TX13: J113.3, U98.~AD12
ARTEMIS_~AD12/TX14: J122.3, U106.~AD12
ARTEMIS_~AD12/TX15: J131.3, U114.~AD12
ARTEMIS_~AD13: J59.4, U50.~AD32
ARTEMIS_~AD13/RX1: J4.2, U8.~AD13
ARTEMIS_~AD13/RX2: J13.2, U6.~AD13
ARTEMIS_~AD13/RX3: J23.2, U18.~AD13
ARTEMIS_~AD13/RX4: J32.2, U26.~AD13
ARTEMIS_~AD13/RX5: J41.2, U34.~AD13
ARTEMIS_~AD13/RX6: J50.2, U42.~AD13
ARTEMIS_~AD13/RX7: J59.2, U50.~AD13
ARTEMIS_~AD13/RX8: J68.2, U58.~AD13
ARTEMIS_~AD13/RX9: J77.2, U66.~AD13
ARTEMIS_~AD13/RX10: J86.2, U74.~AD13
ARTEMIS_~AD13/RX11: J95.2, U82.~AD13
ARTEMIS_~AD13/RX12: J104.2, U90.~AD13
ARTEMIS_~AD13/RX13: J113.2, U98.~AD13
ARTEMIS_~AD13/RX14: J122.2, U106.~AD13
ARTEMIS_~AD13/RX15: J131.2, U114.~AD13
ARTEMIS_~AD14: J68.1, U58.~AD11
ARTEMIS_~AD15: J68.4, U58.~AD32
ARTEMIS_~AD16: J77.1, U66.~AD11
ARTEMIS_~AD17: J77.4, U66.~AD32
ARTEMIS_~AD18: J86.1, U74.~AD11
ARTEMIS_~AD19: J86.4, U74.~AD32
ARTEMIS_~AD20: J95.1, U82.~AD11
ARTEMIS_~AD21: J95.4, U82.~AD32
ARTEMIS_~AD22: J104.1, U90.~AD11
ARTEMIS_~AD23: J104.4, U90.~AD32
ARTEMIS_~AD24: J113.1, U98.~AD11
ARTEMIS_~AD25: J113.4, U98.~AD32
ARTEMIS_~AD26: J122.1, U106.~AD11
ARTEMIS_~AD27: J122.4, U106.~AD32
ARTEMIS_~AD28: J131.1, U114.~AD11
ARTEMIS_~AD29: J131.4, U114.~AD32
ARTEMIS_~AD32: J4.4, U8.~AD32
CC1: J15.B5, R15.2
CC2: J15.A5, R16.2
CC3: J5.B5, R26.2
CC4: J5.A5, R27.2
CC5: J24.B5, R55.2
CC6: J24.A5, R56.2
CC7: J33.B5, R79.2
CC8: J33.A5, R80.2
CC9: J42.B5, R103.2
CC10: J42.A5, R104.2
CC11: J51.B5, R127.2
CC12: J51.A5, R128.2
CC13: J60.B5, R151.2
CC14: J60.A5, R152.2
CC15: J69.B5, R175.2
CC16: J69.A5, R176.2
CC17: J78.B5, R199.2
CC18: J78.A5, R200.2
CC19: J87.B5, R223.2
CC20: J87.A5, R224.2
CC21: J96.B5, R247.2
CC22: J96.A5, R248.2
CC23: J105.B5, R271.2
CC24: J105.A5, R272.2
CC25: J114.B5, R295.2
CC26: J114.A5, R296.2
CC27: J123.B5, R319.2
CC28: J123.A5, R320.2
CC29: J132.B5, R343.2
CC30: J132.A5, R344.2
CHG_LED: R5.1, U2.1
CHG_LED1: R10.1, U5.1
CHG_LED2: R50.1, U17.1
CHG_LED3: R74.1, U25.1
CHG_LED4: R98.1, U33.1
CHG_LED5: R122.1, U41.1
CHG_LED6: R146.1, U49.1
CHG_LED7: R170.1, U57.1
CHG_LED8: R194.1, U65.1
CHG_LED9: R218.1, U73.1
CHG_LED10: R242.1, U81.1
CHG_LED11: R266.1, U89.1
CHG_LED12: R290.1, U97.1
CHG_LED13: R314.1, U105.1
CHG_LED14: R338.1, U113.1
D+1: J15.A6, J15.B6, U7.1
D+2: J5.A6, J5.B6, U10.1
D+3: J24.A6, J24.B6, U19.1
D+4: J33.A6, J33.B6, U27.1
D+5: J42.A6, J42.B6, U35.1
D+6: J51.A6, J51.B6, U43.1
D+7: J60.A6, J60.B6, U51.1
D+8: J69.A6, J69.B6, U59.1
D+9: J78.A6, J78.B6, U67.1
D+10: J87.A6, J87.B6, U75.1
D+11: J96.A6, J96.B6, U83.1
D+12: J105.A6, J105.B6, U91.1
D+13: J114.A6, J114.B6, U99.1
D+14: J123.A6, J123.B6, U107.1
D+15: J132.A6, J132.B6, U115.1
D-1: J15.A7, J15.B7, U7.2
D-2: J5.A7, J5.B7, U10.2
D-3: J24.A7, J24.B7, U19.2
D-4: J33.A7, J33.B7, U27.2
D-5: J42.A7, J42.B7, U35.2
D-6: J51.A7, J51.B7, U43.2
D-7: J60.A7, J60.B7, U51.2
D-8: J69.A7, J69.B7, U59.2
D-9: J78.A7, J78.B7, U67.2
D-10: J87.A7, J87.B7, U75.2
D-11: J96.A7, J96.B7, U83.2
D-12: J105.A7, J105.B7, U91.2
D-13: J114.A7, J114.B7, U99.2
D-14: J123.A7, J123.B7, U107.2
D-15: J132.A7, J132.B7, U115.2
DAT1: J6.DAT1, U8.~D26
DAT2: J6.DAT2, U8.~D4
DAT3: J17.DAT1, U6.~D26
DAT4: J17.DAT2, U6.~D4
DAT5: J26.DAT1, U18.~D26
DAT6: J26.DAT2, U18.~D4
DAT7: J35.DAT1, U26.~D26
DAT8: J35.DAT2, U26.~D4
DAT9: J44.DAT1, U34.~D26
DAT10: J44.DAT2, U34.~D4
DAT11: J53.DAT1, U42.~D26
DAT12: J53.DAT2, U42.~D4
DAT13: J62.DAT1, U50.~D26
DAT14: J62.DAT2, U50.~D4
DAT15: J71.DAT1, U58.~D26
DAT16: J71.DAT2, U58.~D4
DAT17: J80.DAT1, U66.~D26
DAT18: J80.DAT2, U66.~D4
DAT19: J89.DAT1, U74.~D26
DAT20: J89.DAT2, U74.~D4
DAT21: J98.DAT1, U82.~D26
DAT22: J98.DAT2, U82.~D4
DAT23: J107.DAT1, U90.~D26
DAT24: J107.DAT2, U90.~D4
DAT25: J116.DAT1, U98.~D26
DAT26: J116.DAT2, U98.~D4
DAT27: J125.DAT1, U106.~D26
DAT28: J125.DAT2, U106.~D4
DAT29: J134.DAT1, U114.~D26
DAT30: J134.DAT2, U114.~D4
GND: BT1.-, C1.2, C2.2, C3.2, C4.2, C5.2, C7.2, C29.1, C30.1, C31.1, C32.2, C33.2, C40.2, C41.2, C44.2, C46.2, C51.2, C52.2, C53.2, C54.2, D9.C, GND.P$1, J1.2, J2.1, J3.2, J4.6, J5.GND, J5.GND2, J6.CD1, J6.GND, J6.GND1, J6.GND3, J11.1, J14.3, J14.5, J14.9, LED1.C, R3.1, R4.1, R6.1, R8.1, R26.1, R27.1, R29.1, S3.1, S3.2, U1.1, U2.2, U3.2, U4.2, U8.GND@1, U8.GND@22, U8.GND@38, U8.GND@39, U8.GND@47, U8.GND@59, U10.3, U13.18, U13.20, U14.2
GND1: BT2.-, C6.2, C8.2, C9.1, C10.1, C11.1, C12.2, C13.2, C14.2, C15.2, C18.2, C19.2, C20.2, C21.2, C22.2, C23.2, C24.2, C25.2, C26.2, C27.2, D5.C, GND1.P$1, J8.3, J8.5, J8.9, J9.1, J10.1, J12.2, J13.6, J15.GND, J15.GND2, J16.2, J17.CD1, J17.GND, J17.GND1, J17.GND3, LED2.C, R9.1, R15.1, R16.1, R18.1, R37.1, R38.1, R42.1, S1.1, S1.2, U5.2, U6.GND@1, U6.GND@22, U6.GND@38, U6.GND@39, U6.GND@47, U6.GND@59, U7.3, U9.18, U9.20, U11.2, U12.2, U15.1, U16.2
GND2: BT3.-, C28.2, C34.2, C35.1, C36.1, C37.1, C38.2, C39.2, C45.2, C47.2, C50.2, C55.2, C56.2, C57.2, C58.2, C59.2, C60.2, C61.2, C62.2, C63.2, D16.C, GND2.P$1, J19.3, J19.5, J19.9, J20.1, J21.1, J22.2, J23.6, J24.GND, J24.GND2, J25.2, J26.CD1, J26.GND, J26.GND1, J26.GND3, LED3.C, R43.1, R55.1, R56.1, R58.1, R69.1, R70.1, R72.1, S2.1, S2.2, U17.2, U18.GND@1, U18.GND@22, U18.GND@38, U18.GND@39, U18.GND@47, U18.GND@59, U19.3, U20.18, U20.20, U21.2, U22.2, U23.1, U24.2
GND3: BT4.-, C64.2, C65.2, C66.1, C67.1, C68.1, C69.2, C70.2, C71.2, C72.2, C75.2, C76.2, C77.2, C78.2, C79.2, C80.2, C81.2, C82.2, C83.2, C84.2, D23.C, GND3.P$1, J28.3, J28.5, J28.9, J29.1, J30.1, J31.2, J32.6, J33.GND, J33.GND2, J34.2, J35.CD1, J35.GND, J35.GND1, J35.GND3, LED4.C, R73.1, R79.1, R80.1, R82.1, R93.1, R94.1, R96.1, S4.1, S4.2, U25.2, U26.GND@1, U26.GND@22, U26.GND@38, U26.GND@39, U26.GND@47, U26.GND@59, U27.3, U28.18, U28.20, U29.2, U30.2, U31.1, U32.2
GND4: BT5.-, C85.2, C86.2, C87.1, C88.1, C89.1, C90.2, C91.2, C92.2, C93.2, C96.2, C97.2, C98.2, C99.2, C100.2, C101.2, C102.2, C103.2, C104.2, C105.2, D30.C, GND4.P$1, J37.3, J37.5, J37.9, J38.1, J39.1, J40.2, J41.6, J42.GND, J42.GND2, J43.2, J44.CD1, J44.GND, J44.GND1, J44.GND3, LED5.C, R97.1, R103.1, R104.1, R106.1, R117.1, R118.1, R120.1, S5.1, S5.2, U33.2, U34.GND@1, U34.GND@22, U34.GND@38, U34.GND@39, U34.GND@47, U34.GND@59, U35.3, U36.18, U36.20, U37.2, U38.2, U39.1, U40.2
GND5: BT6.-, C106.2, C107.2, C108.1, C109.1, C110.1, C111.2, C112.2, C113.2, C114.2, C117.2, C118.2, C119.2, C120.2, C121.2, C122.2, C123.2, C124.2, C125.2, C126.2, D37.C, GND5.P$1, J46.3, J46.5, J46.9, J47.1, J48.1, J49.2, J50.6, J51.GND, J51.GND2, J52.2, J53.CD1, J53.GND, J53.GND1, J53.GND3, LED6.C, R121.1, R127.1, R128.1, R130.1, R141.1, R142.1, R144.1, S6.1, S6.2, U41.2, U42.GND@1, U42.GND@22, U42.GND@38, U42.GND@39, U42.GND@47, U42.GND@59, U43.3, U44.18, U44.20, U45.2, U46.2, U47.1, U48.2
GND6: BT7.-, C127.2, C128.2, C129.1, C130.1, C131.1, C132.2, C133.2, C134.2, C135.2, C138.2, C139.2, C140.2, C141.2, C142.2, C143.2, C144.2, C145.2, C146.2, C147.2, D44.C, GND6.P$1, J55.3, J55.5, J55.9, J56.1, J57.1, J58.2, J59.6, J60.GND, J60.GND2, J61.2, J62.CD1, J62.GND, J62.GND1, J62.GND3, LED7.C, R145.1, R151.1, R152.1, R154.1, R165.1, R166.1, R168.1, S7.1, S7.2, U49.2, U50.GND@1, U50.GND@22, U50.GND@38, U50.GND@39, U50.GND@47, U50.GND@59, U51.3, U52.18, U52.20, U53.2, U54.2, U55.1, U56.2
GND7: BT8.-, C148.2, C149.2, C150.1, C151.1, C152.1, C153.2, C154.2, C155.2, C156.2, C159.2, C160.2, C161.2, C162.2, C163.2, C164.2, C165.2, C166.2, C167.2, C168.2, D51.C, GND7.P$1, J64.3, J64.5, J64.9, J65.1, J66.1, J67.2, J68.6, J69.GND, J69.GND2, J70.2, J71.CD1, J71.GND, J71.GND1, J71.GND3, LED8.C, R169.1, R175.1, R176.1, R178.1, R189.1, R190.1, R192.1, S8.1, S8.2, U57.2, U58.GND@1, U58.GND@22, U58.GND@38, U58.GND@39, U58.GND@47, U58.GND@59, U59.3, U60.18, U60.20, U61.2, U62.2, U63.1, U64.2
GND8: BT9.-, C169.2, C170.2, C171.1, C172.1, C173.1, C174.2, C175.2, C176.2, C177.2, C180.2, C181.2, C182.2, C183.2, C184.2, C185.2, C186.2, C187.2, C188.2, C189.2, D58.C, GND8.P$1, J73.3, J73.5, J73.9, J74.1, J75.1, J76.2, J77.6, J78.GND, J78.GND2, J79.2, J80.CD1, J80.GND, J80.GND1, J80.GND3, LED9.C, R193.1, R199.1, R200.1, R202.1, R213.1, R214.1, R216.1, S9.1, S9.2, U65.2, U66.GND@1, U66.GND@22, U66.GND@38, U66.GND@39, U66.GND@47, U66.GND@59, U67.3, U68.18, U68.20, U69.2, U70.2, U71.1, U72.2
GND9: BT10.-, C190.2, C191.2, C192.1, C193.1, C194.1, C195.2, C196.2, C197.2, C198.2, C201.2, C202.2, C203.2, C204.2, C205.2, C206.2, C207.2, C208.2, C209.2, C210.2, D65.C, GND9.P$1, J82.3, J82.5, J82.9, J83.1, J84.1, J85.2, J86.6, J87.GND, J87.GND2, J88.2, J89.CD1, J89.GND, J89.GND1, J89.GND3, LED10.C, R217.1, R223.1, R224.1, R226.1, R237.1, R238.1, R240.1, S10.1, S10.2, U73.2, U74.GND@1, U74.GND@22, U74.GND@38, U74.GND@39, U74.GND@47, U74.GND@59, U75.3, U76.18, U76.20, U77.2, U78.2, U79.1, U80.2
GND10: BT11.-, C211.2, C212.2, C213.1, C214.1, C215.1, C216.2, C217.2, C218.2, C219.2, C222.2, C223.2, C224.2, C225.2, C226.2, C227.2, C228.2, C229.2, C230.2, C231.2, D72.C, GND10.P$1, J91.3, J91.5, J91.9, J92.1, J93.1, J94.2, J95.6, J96.GND, J96.GND2, J97.2, J98.CD1, J98.GND, J98.GND1, J98.GND3, LED11.C, R241.1, R247.1, R248.1, R250.1, R261.1, R262.1, R264.1, S11.1, S11.2, U81.2, U82.GND@1, U82.GND@22, U82.GND@38, U82.GND@39, U82.GND@47, U82.GND@59, U83.3, U84.18, U84.20, U85.2, U86.2, U87.1, U88.2
GND11: BT12.-, C232.2, C233.2, C234.1, C235.1, C236.1, C237.2, C238.2, C239.2, C240.2, C243.2, C244.2, C245.2, C246.2, C247.2, C248.2, C249.2, C250.2, C251.2, C252.2, D79.C, GND11.P$1, J100.3, J100.5, J100.9, J101.1, J102.1, J103.2, J104.6, J105.GND, J105.GND2, J106.2, J107.CD1, J107.GND, J107.GND1, J107.GND3, LED12.C, R265.1, R271.1, R272.1, R274.1, R285.1, R286.1, R288.1, S12.1, S12.2, U89.2, U90.GND@1, U90.GND@22, U90.GND@38, U90.GND@39, U90.GND@47, U90.GND@59, U91.3, U92.18, U92.20, U93.2, U94.2, U95.1, U96.2
GND12: BT13.-, C253.2, C254.2, C255.1, C256.1, C257.1, C258.2, C259.2, C260.2, C261.2, C264.2, C265.2, C266.2, C267.2, C268.2, C269.2, C270.2, C271.2, C272.2, C273.2, D86.C, GND12.P$1, J109.3, J109.5, J109.9, J110.1, J111.1, J112.2, J113.6, J114.GND, J114.GND2, J115.2, J116.CD1, J116.GND, J116.GND1, J116.GND3, LED13.C, R289.1, R295.1, R296.1, R298.1, R309.1, R310.1, R312.1, S13.1, S13.2, U97.2, U98.GND@1, U98.GND@22, U98.GND@38, U98.GND@39, U98.GND@47, U98.GND@59, U99.3, U100.18, U100.20, U101.2, U102.2, U103.1, U104.2
GND13: BT14.-, C274.2, C275.2, C276.1, C277.1, C278.1, C279.2, C280.2, C281.2, C282.2, C285.2, C286.2, C287.2, C288.2, C289.2, C290.2, C291.2, C292.2, C293.2, C294.2, D93.C, GND13.P$1, J118.3, J118.5, J118.9, J119.1, J120.1, J121.2, J122.6, J123.GND, J123.GND2, J124.2, J125.CD1, J125.GND, J125.GND1, J125.GND3, LED14.C, R313.1, R319.1, R320.1, R322.1, R333.1, R334.1, R336.1, S14.1, S14.2, U105.2, U106.GND@1, U106.GND@22, U106.GND@38, U106.GND@39, U106.GND@47, U106.GND@59, U107.3, U108.18, U108.20, U109.2, U110.2, U111.1, U112.2
GND14: BT15.-, C295.2, C296.2, C297.1, C298.1, C299.1, C300.2, C301.2, C302.2, C303.2, C306.2, C307.2, C308.2, C309.2, C310.2, C311.2, C312.2, C313.2, C314.2, C315.2, D100.C, GND14.P$1, J127.3, J127.5, J127.9, J128.1, J129.1, J130.2, J131.6, J132.GND, J132.GND2, J133.2, J134.CD1, J134.GND, J134.GND1, J134.GND3, LED15.C, R337.1, R343.1, R344.1, R346.1, R357.1, R358.1, R360.1, S15.1, S15.2, U113.2, U114.GND@1, U114.GND@22, U114.GND@38, U114.GND@39, U114.GND@47, U114.GND@59, U115.3, U116.18, U116.20, U117.2, U118.2, U119.1, U120.2
ICM-20948-LV_!CS!: Q9.2, R46.1, U13.22
ICM-20948-LV_!CS!1: Q8.2, R31.1, U9.22
ICM-20948-LV_!CS!2: Q16.2, R63.1, U20.22
ICM-20948-LV_!CS!3: Q22.2, R87.1, U28.22
ICM-20948-LV_!CS!4: Q28.2, R111.1, U36.22
ICM-20948-LV_!CS!5: Q34.2, R135.1, U44.22
ICM-20948-LV_!CS!6: Q40.2, R159.1, U52.22
ICM-20948-LV_!CS!7: Q46.2, R183.1, U60.22
ICM-20948-LV_!CS!8: Q52.2, R207.1, U68.22
ICM-20948-LV_!CS!9: Q58.2, R231.1, U76.22
ICM-20948-LV_!CS!10: Q64.2, R255.1, U84.22
ICM-20948-LV_!CS!11: Q70.2, R279.1, U92.22
ICM-20948-LV_!CS!12: Q76.2, R303.1, U100.22
ICM-20948-LV_!CS!13: Q82.2, R327.1, U108.22
ICM-20948-LV_!CS!14: Q88.2, R351.1, U116.22
ICM-20948-LV_#_1.8V: C52.1, C53.1, Q1.1, Q3.1, Q7.1, Q9.1, Q10.1, R40.2, R41.2, R44.2, R46.2, R48.2, U13.8, U13.13, U14.5
ICM-20948-LV_#_1.8V1: C21.1, C22.1, Q4.1, Q5.1, Q6.1, Q8.1, Q11.1, R19.2, R20.2, R21.2, R31.2, R33.2, U9.8, U9.13, U11.5
ICM-20948-LV_#_1.8V2: C57.1, C58.1, Q13.1, Q14.1, Q15.1, Q16.1, Q17.1, R59.2, R60.2, R61.2, R63.2, R65.2, U20.8, U20.13, U21.5
ICM-20948-LV_#_1.8V3: C78.1, C79.1, Q19.1, Q20.1, Q21.1, Q22.1, Q23.1, R83.2, R84.2, R85.2, R87.2, R89.2, U28.8, U28.13, U29.5
ICM-20948-LV_#_1.8V4: C99.1, C100.1, Q25.1, Q26.1, Q27.1, Q28.1, Q29.1, R107.2, R108.2, R109.2, R111.2, R113.2, U36.8, U36.13, U37.5
ICM-20948-LV_#_1.8V5: C120.1, C121.1, Q31.1, Q32.1, Q33.1, Q34.1, Q35.1, R131.2, R132.2, R133.2, R135.2, R137.2, U44.8, U44.13, U45.5
ICM-20948-LV_#_1.8V6: C141.1, C142.1, Q37.1, Q38.1, Q39.1, Q40.1, Q41.1, R155.2, R156.2, R157.2, R159.2, R161.2, U52.8, U52.13, U53.5
ICM-20948-LV_#_1.8V7: C162.1, C163.1, Q43.1, Q44.1, Q45.1, Q46.1, Q47.1, R179.2, R180.2, R181.2, R183.2, R185.2, U60.8, U60.13, U61.5
ICM-20948-LV_#_1.8V8: C183.1, C184.1, Q49.1, Q50.1, Q51.1, Q52.1, Q53.1, R203.2, R204.2, R205.2, R207.2, R209.2, U68.8, U68.13, U69.5
ICM-20948-LV_#_1.8V9: C204.1, C205.1, Q55.1, Q56.1, Q57.1, Q58.1, Q59.1, R227.2, R228.2, R229.2, R231.2, R233.2, U76.8, U76.13, U77.5
ICM-20948-LV_#_1.8V10: C225.1, C226.1, Q61.1, Q62.1, Q63.1, Q64.1, Q65.1, R251.2, R252.2, R253.2, R255.2, R257.2, U84.8, U84.13, U85.5
ICM-20948-LV_#_1.8V11: C246.1, C247.1, Q67.1, Q68.1, Q69.1, Q70.1, Q71.1, R275.2, R276.2, R277.2, R279.2, R281.2, U92.8, U92.13, U93.5
ICM-20948-LV_#_1.8V12: C267.1, C268.1, Q73.1, Q74.1, Q75.1, Q76.1, Q77.1, R299.2, R300.2, R301.2, R303.2, R305.2, U100.8, U100.13, U101.5
ICM-20948-LV_#_1.8V13: C288.1, C289.1, Q79.1, Q80.1, Q81.1, Q82.1, Q83.1, R323.2, R324.2, R325.2, R327.2, R329.2, U108.8, U108.13, U109.5
ICM-20948-LV_#_1.8V14: C309.1, C310.1, Q85.1, Q86.1, Q87.1, Q88.1, Q89.1, R347.2, R348.2, R349.2, R351.2, R353.2, U116.8, U116.13, U117.5
ICM-20948-LV_INT: Q7.2, R44.1, U13.12
ICM-20948-LV_INT1: Q6.2, R21.1, U9.12
ICM-20948-LV_INT2: Q15.2, R61.1, U20.12
ICM-20948-LV_INT3: Q21.2, R85.1, U28.12
ICM-20948-LV_INT4: Q27.2, R109.1, U36.12
ICM-20948-LV_INT5: Q33.2, R133.1, U44.12
ICM-20948-LV_INT6: Q39.2, R157.1, U52.12
ICM-20948-LV_INT7: Q45.2, R181.1, U60.12
ICM-20948-LV_INT8: Q51.2, R205.1, U68.12
ICM-20948-LV_INT9: Q57.2, R229.1, U76.12
ICM-20948-LV_INT10: Q63.2, R253.1, U84.12
ICM-20948-LV_INT11: Q69.2, R277.1, U92.12
ICM-20948-LV_INT12: Q75.2, R301.1, U100.12
ICM-20948-LV_INT13: Q81.2, R325.1, U108.12
ICM-20948-LV_INT14: Q87.2, R349.1, U116.12
ICM-20948-LV_SCK: Q1.2, R40.1, U13.23
ICM-20948-LV_SCK1: Q4.2, R19.1, U9.23
ICM-20948-LV_SCK2: Q13.2, R59.1, U20.23
ICM-20948-LV_SCK3: Q19.2, R83.1, U28.23
ICM-20948-LV_SCK4: Q25.2, R107.1, U36.23
ICM-20948-LV_SCK5: Q31.2, R131.1, U44.23
ICM-20948-LV_SCK6: Q37.2, R155.1, U52.23
ICM-20948-LV_SCK7: Q43.2, R179.1, U60.23
ICM-20948-LV_SCK8: Q49.2, R203.1, U68.23
ICM-20948-LV_SCK9: Q55.2, R227.1, U76.23
ICM-20948-LV_SCK10: Q61.2, R251.1, U84.23
ICM-20948-LV_SCK11: Q67.2, R275.1, U92.23
ICM-20948-LV_SCK12: Q73.2, R299.1, U100.23
ICM-20948-LV_SCK13: Q79.2, R323.1, U108.23
ICM-20948-LV_SCK14: Q85.2, R347.1, U116.23
ICM-20948-LV_SDI: Q3.2, R41.1, U13.24
ICM-20948-LV_SDI1: Q5.2, R20.1, U9.24
ICM-20948-LV_SDI2: Q14.2, R60.1, U20.24
ICM-20948-LV_SDI3: Q20.2, R84.1, U28.24
ICM-20948-LV_SDI4: Q26.2, R108.1, U36.24
ICM-20948-LV_SDI5: Q32.2, R132.1, U44.24
ICM-20948-LV_SDI6: Q38.2, R156.1, U52.24
ICM-20948-LV_SDI7: Q44.2, R180.1, U60.24
ICM-20948-LV_SDI8: Q50.2, R204.1, U68.24
ICM-20948-LV_SDI9: Q56.2, R228.1, U76.24
ICM-20948-LV_SDI10: Q62.2, R252.1, U84.24
ICM-20948-LV_SDI11: Q68.2, R276.1, U92.24
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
